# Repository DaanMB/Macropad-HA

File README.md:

<h2>A macropad that controls home assistant using espHome.</h2>
<p>This is NOT a Hackpad</p> 

<br>

<br>

<br>
<a href="https://youtu.be/JzanmzNsBhA](https://www.youtube.com/watch?v=KuiGH0L9EsM"> See working here</a>
<p>I made this project to control parts of my pc with a macropad and my conclusion was that the things i wanted to do with a macropad where best achevable with espHome. The only problem with using espHome is that somtimes the buttons ghost press or double press, i dont know if thats a skill isue of me or espHome.</p>
<h2>Features</h2>
<p>
  1. 4x4 buttons that are programmable in HA. <br>
  2. An 128X64 oled screen that displays time and whats playing on spotify using a HA spotify intergration. <br>
  3. 2 rgb leds that are programmable in HA. <br>
  4. 2 potentiometers that are programmable in HA</p>
  <br>

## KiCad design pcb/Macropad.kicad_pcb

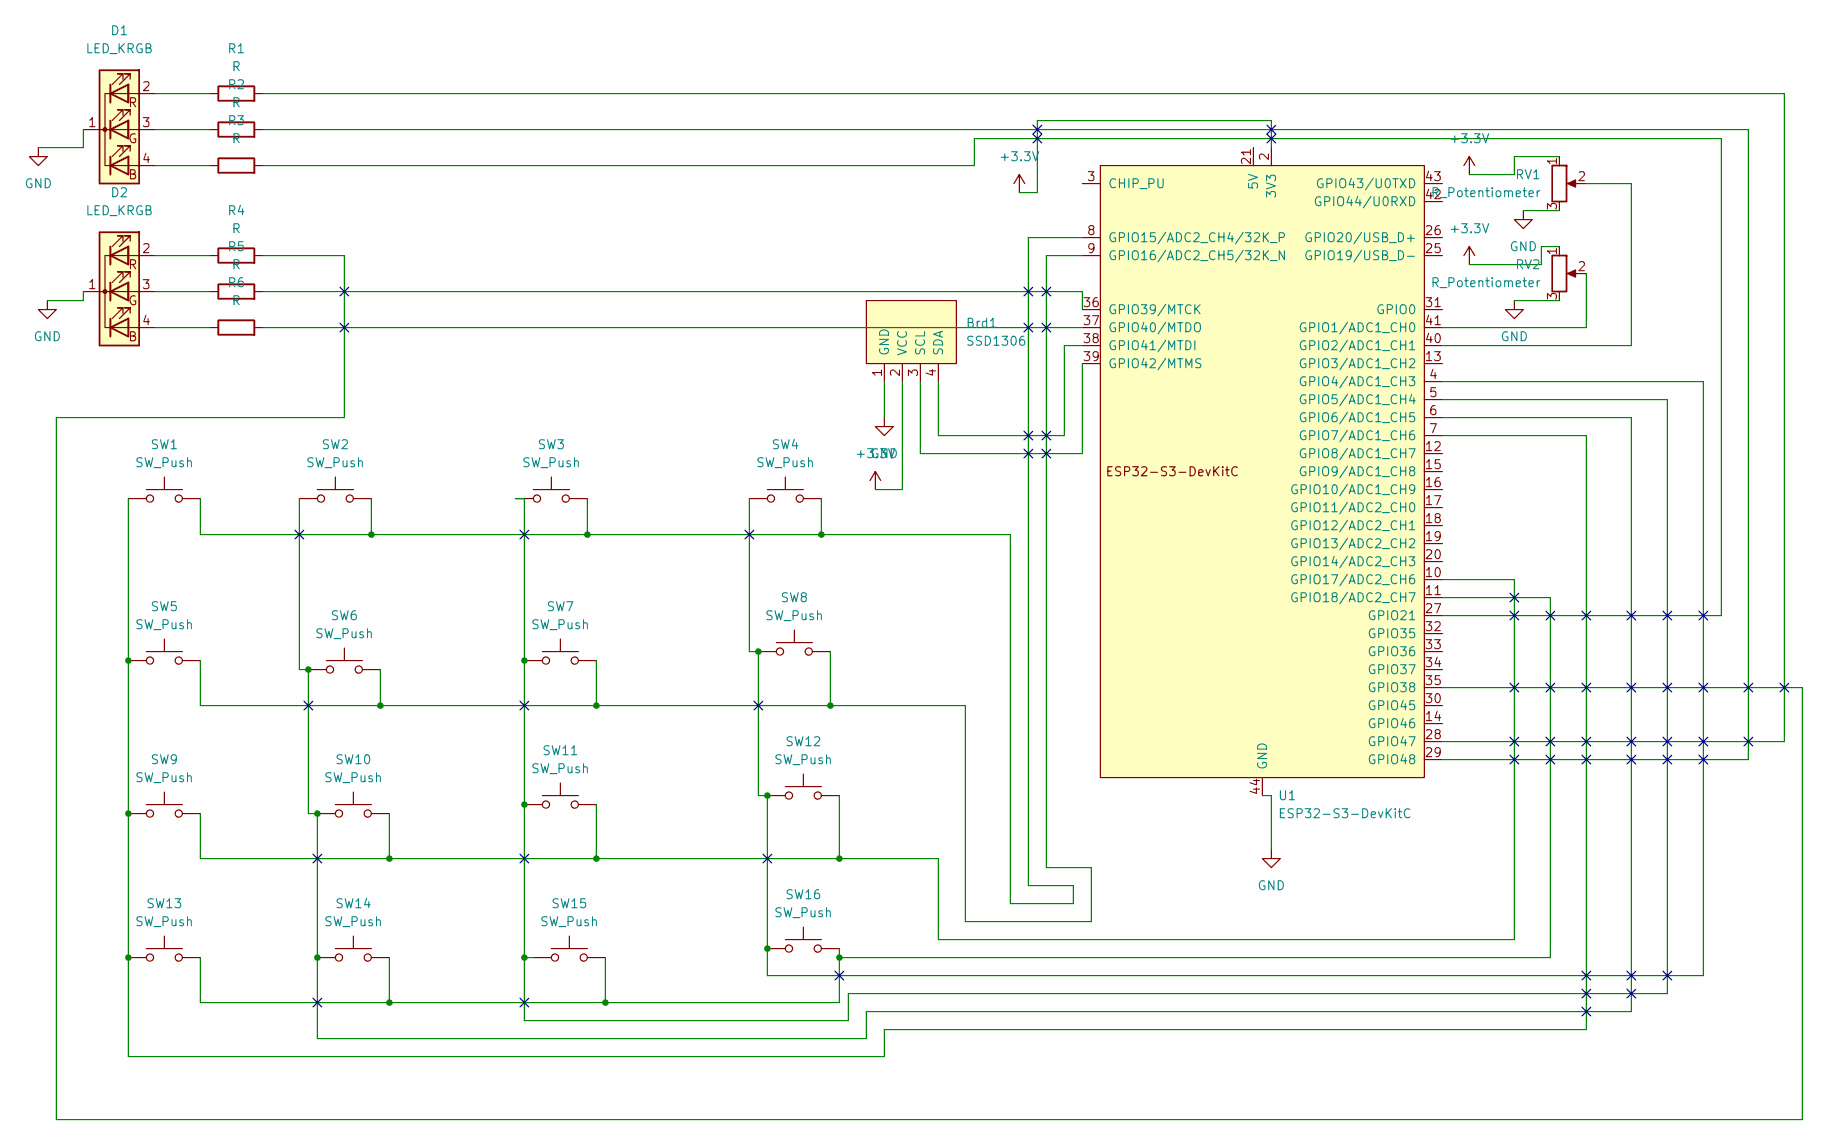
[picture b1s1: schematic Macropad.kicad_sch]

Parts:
Brd1: SSD1306; 128x64OLED
D1, D2: LED_KRGB; LED_D5.0mm-4_RGB_Staggered_Pins
R1, R2, R3, R4, R5, R6: R; R_Axial_DIN0207_L6.3mm_D2.5mm_P10.16mm_Horizontal
RV1, RV2: R_Potentiometer; TRIM_WH148-1A-2-18T-L20
SW1, SW2, SW3, SW4, SW5, SW6, SW7, SW8, SW9, SW10, SW11, SW12, SW13, SW14, SW15, SW16: SW_Push; SW_Cherry_MX_1.00u_PCB
U1: ESP32-S3-DevKitC

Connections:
+3.3V: Brd1.2 (VCC), RV1.1, RV2.1, U1.1 (3V3), U1.2 (3V3)
GND: Brd1.1 (GND), D1.1 (K), D2.1 (K), RV1.3, RV2.3, U1.22 (GND), U1.23 (GND), U1.24 (GND), U1.44 (GND)
unnamed: Brd1.3 (SCL), U1.39 (GPIO42/MTMS)
unnamed: Brd1.4 (SDA), U1.38 (GPIO41/MTDI)
unnamed: D1.4 (BA), R3.1
unnamed: D1.3 (GA), R2.1
unnamed: D1.2 (RA), R1.1
unnamed: D2.4 (BA), R6.1
unnamed: D2.3 (GA), R5.1
unnamed: D2.2 (RA), R4.1
unnamed: RV2.2, U1.41 (GPIO1/ADC1_CH0)
unnamed: RV1.2, U1.40 (GPIO2/ADC1_CH1)
unnamed: SW4.1, SW8.1, SW12.1, SW16.1, U1.4 (GPIO4/ADC1_CH3)
unnamed: SW3.1, SW7.1, SW11.1, SW15.1, U1.5 (GPIO5/ADC1_CH4)
unnamed: SW2.1, SW6.1, SW10.1, SW14.1, U1.6 (GPIO6/ADC1_CH5)
unnamed: SW1.1, SW5.1, SW9.1, SW13.1, U1.7 (GPIO7/ADC1_CH6)
unnamed: SW1.2, SW2.2, SW3.2, SW4.2, U1.8 (GPIO15/ADC2_CH4/32K_P)
unnamed: SW5.2, SW6.2, SW7.2, SW8.2, U1.9 (GPIO16/ADC2_CH5/32K_N)
unnamed: SW9.2, SW10.2, SW11.2, SW12.2, U1.10 (GPIO17/ADC2_CH6)
unnamed: SW13.2, SW14.2, SW15.2, SW16.2, U1.11 (GPIO18/ADC2_CH7)
unnamed: R3.2, U1.27 (GPIO21)
unnamed: R4.2, U1.35 (GPIO38)
unnamed: R5.2, U1.36 (GPIO39/MTCK)
unnamed: R6.2, U1.37 (GPIO40/MTDO)
unnamed: R1.2, U1.28 (GPIO47)
unnamed: R2.2, U1.29 (GPIO48)

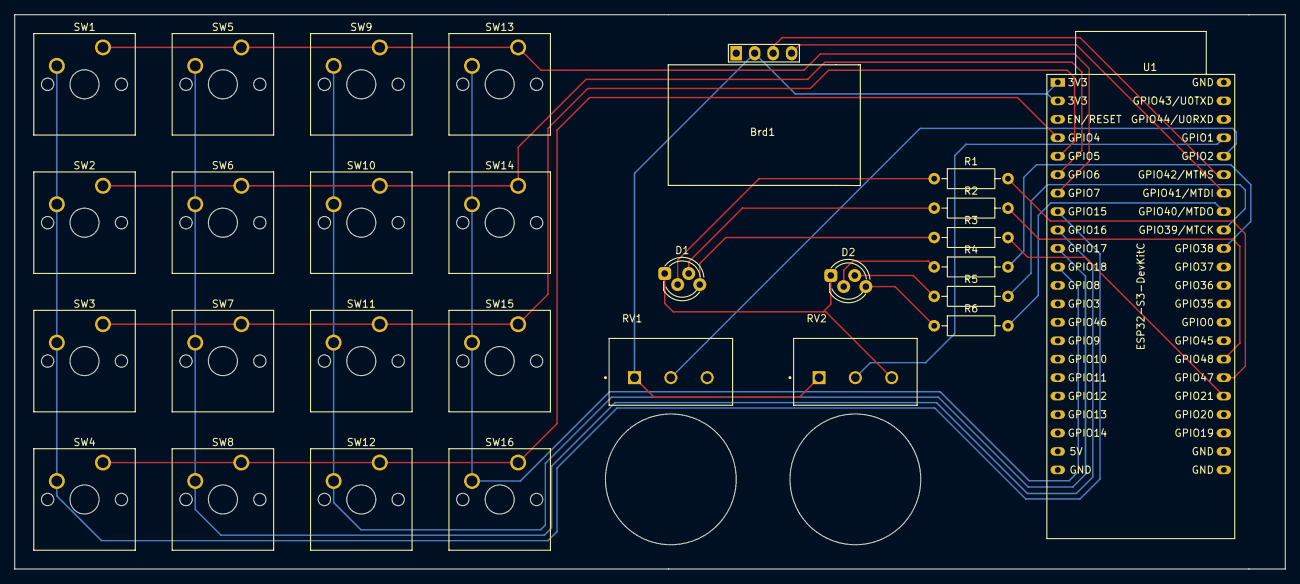
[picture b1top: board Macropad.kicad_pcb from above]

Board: 2 copper layers, 174.9 x 76.3 mm, 28 parts (0 on the bottom side), 26 nets.

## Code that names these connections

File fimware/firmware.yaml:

esphome:
  name: my-esp32 

esp32:
  board: esp32-s3-devkitc-1
  framework:
    type: esp-idf
  variant: esp32s3

wifi:
  ssid: "SSID"
  password: "PASSWORD"

logger:
api:
ota:
  - platform: esphome
    password: "PASSWORD"

i2c:
  sda: GPIO41
  scl: GPIO42
  scan: true
  id: bus_a

time:
  - platform: homeassistant
    id: ha_time

sensor:
  - platform: adc
    pin: GPIO1
    name: "Potmeter 1"
    id: pot1
    update_interval: 200ms
    attenuation: 12db
    unit_of_measurement: "%"
    filters:
      - sliding_window_moving_average:
          window_size: 5
          send_every: 1
      - calibrate_linear:
          datapoints:
            - 0.0 -> 0.0
            - 3.13 -> 100.0
      - clamp:
          min_value: 0
          max_value: 100
          ignore_out_of_range: false
      - round: 0
      - delta: 2
  - platform: adc
    pin: GPIO2
    name: "Potmeter 2"
    id: pot2
    update_interval: 200ms
    attenuation: 12db
    unit_of_measurement: "%"
    filters:
      - sliding_window_moving_average:
          window_size: "5"
          send_every: "1"
      - calibrate_linear:
          datapoints:
            - 0.0 -> 0.00
            - 3.13 -> 100.0
      - clamp:
          min_value: "0"
          max_value: "100"
          ignore_out_of_range: false
      - round: 0
      - delta: 2
text_sensor:
  - platform: homeassistant
    id: spotify_title
    entity_id: media_player.spotify_daniel
    attribute: media_title
  - platform: homeassistant
    id: spotify_artist
    entity_id: media_player.spotify_daniel
    attribute: media_artist

matrix_keypad:
  rows:
    - pin: GPIO4
    - pin: GPIO5
    - pin: GPIO6
    - pin: GPIO7
  columns:
    - pin:
        number: GPIO15
        mode:
          input: true
          pullup: true
    - pin:
        number: GPIO16
        mode:
          input: true
          pullup: true
    - pin:
        number: GPIO17
        mode:
          input: true
          pullup: true
    - pin:
        number: GPIO18
        mode:
          input: true
          pullup: true

  keys: 12345678abcdefgh
binary_sensor:
  - platform: matrix_keypad
    name: "Knop 1"
    key: '1'
  - platform: matrix_keypad
    name: "Knop 2"
    key: '2'
  - platform: matrix_keypad
    name: "Knop 3"
    key: '3'
  - platform: matrix_keypad
    name: "Knop 4"
    key: '4'
  - platform: matrix_keypad
    name: "Knop 5"
    key: '5'
  - platform: matrix_keypad
    name: "Knop 6"
    key: '6'
  - platform: matrix_keypad
    name: "Knop 7"
    key: '7'
  - platform: matrix_keypad
    name: "Knop 8"
    key: '8'
  - platform: matrix_keypad
    name: "Knop 9"
    key: 'a'
  - platform: matrix_keypad
    name: "Knop 10"
    key: 'b'
  - platform: matrix_keypad
    name: "Knop 11"
    key: 'c'
  - platform: matrix_keypad
    name: "Knop 12"
    key: 'd'
  - platform: matrix_keypad
    name: "Knop 13"
    key: 'e'
  - platform: matrix_keypad
    name: "Knop 14"
    key: 'f'
  - platform: matrix_keypad
    name: "Knop 15"
    key: 'g'
  - platform: matrix_keypad
    name: "Knop 16"
    key: 'h'

output:
  - platform: ledc
    pin: GPIO47
    id: led1_red
  - platform: ledc
    pin: GPIO48
    id: led1_green
  - platform: ledc
    pin: GPIO21
    id: led1_blue
    
  - platform: ledc
    pin: GPIO38
    id: led2_red
  - platform: ledc
    pin: GPIO39
    id: led2_green
  - platform: ledc
    pin: GPIO40
    id: led2_blue

light:
  - platform: rgb
    name: "RGB LED 1"
    red: led1_red
    green: led1_green
    blue: led1_blue
  - platform: rgb
    name: "RGB LED 2"
    red: led2_red
    green: led2_green
    blue: led2_blue

font:
  - file: "gfonts://Courier+Prime"
    id: Courier_Prime_10
    size: 10
  - file: "gfonts://Courier+Prime"
    id: Courier_Prime_14
    size: 14
  - file: "gfonts://Courier+Prime"
    id: Courier_Prime_8
    size: 8

display:
  - platform: ssd1306_i2c
    model: SSD1306_128X64
    address: 0x3c
    id: my_display
    update_interval: 1s
    lambda: |-
      //time
      auto time = id(ha_time).now();
      if (time.is_valid()) {
        it.strftime(40, 23, id(Courier_Prime_14), Color(255, 255, 255), "%H:%M", time);
      }

      // Playing + songname
      it.print(4, 44, id(Courier_Prime_10), Color(255, 255, 255), "playing:");
      it.print(54, 44, id(Courier_Prime_10), Color(255, 255, 255), id(spotify_title).state.c_str());

      // By + artiest
      it.print(4, 53, id(Courier_Prime_8), Color(255, 255, 255), "By:");
      it.print(19, 53, id(Courier_Prime_8), Color(255, 255, 255), id(spotify_artist).state.c_str());

      // Line
      it.line(0, 19, 126, 19, Color(255, 255, 255));
      it.line(0, 39, 126, 39, Color(255, 255, 255));
